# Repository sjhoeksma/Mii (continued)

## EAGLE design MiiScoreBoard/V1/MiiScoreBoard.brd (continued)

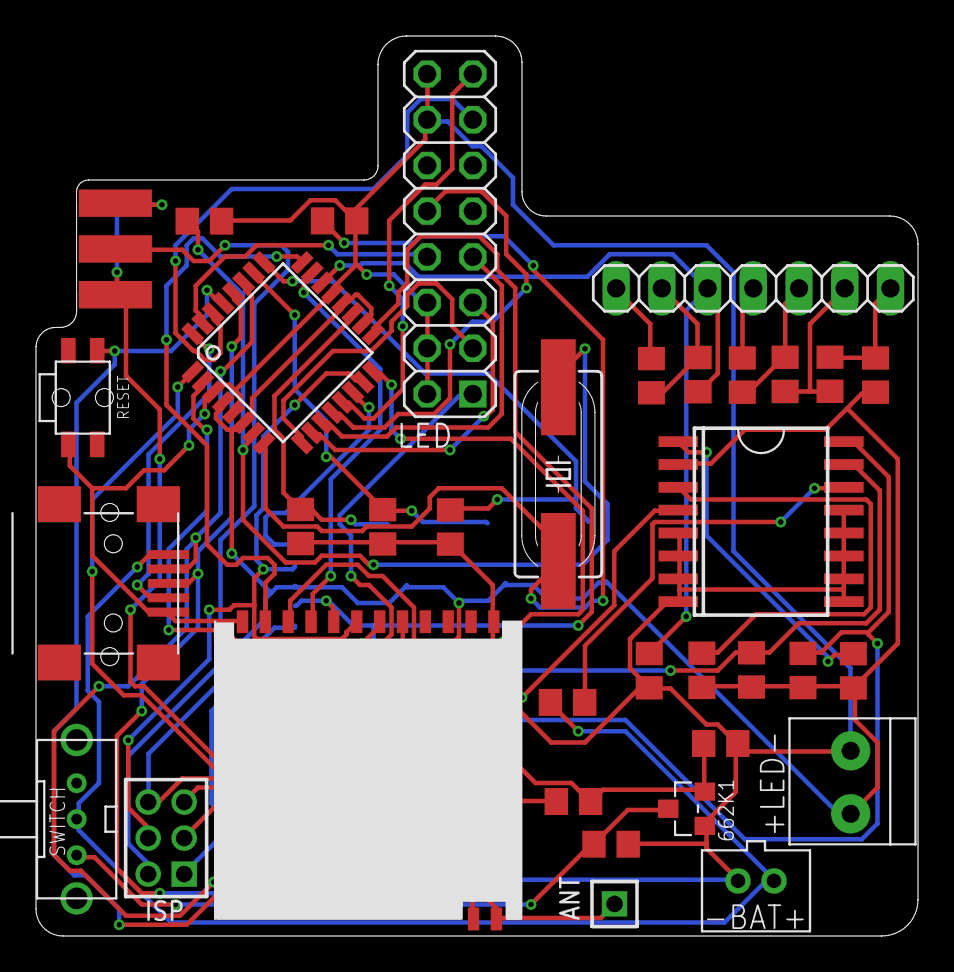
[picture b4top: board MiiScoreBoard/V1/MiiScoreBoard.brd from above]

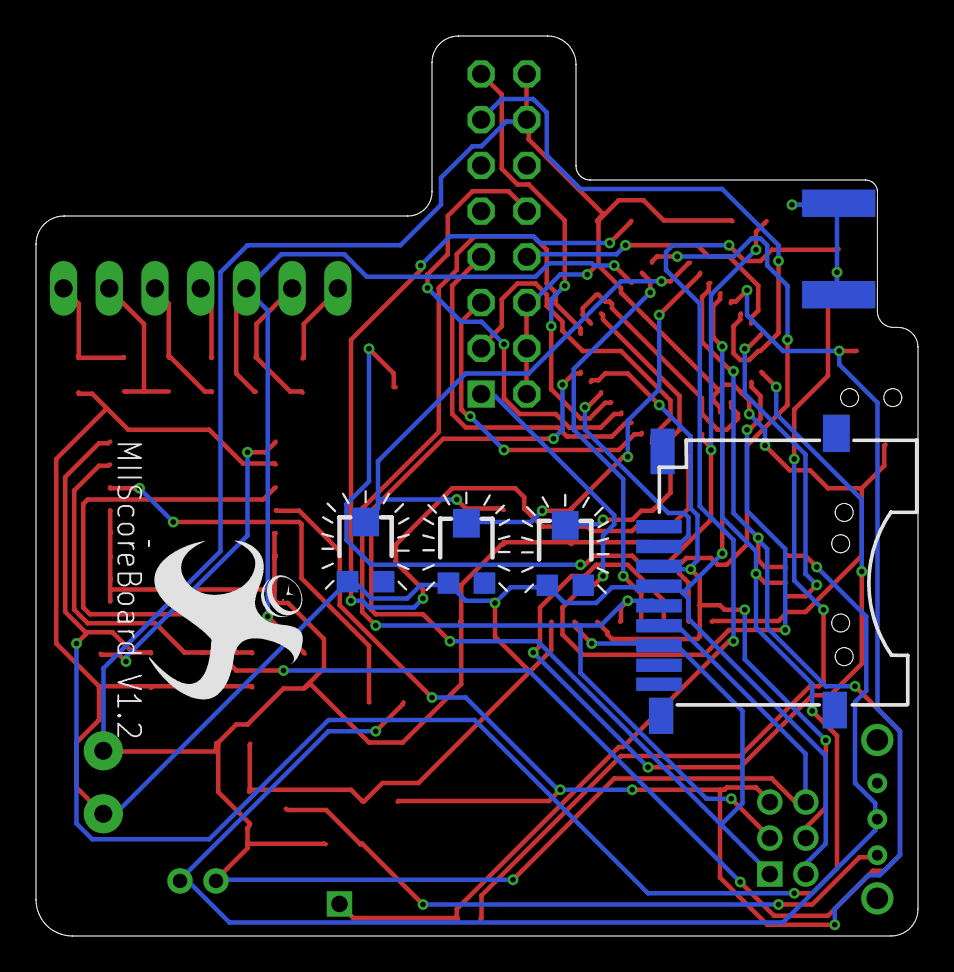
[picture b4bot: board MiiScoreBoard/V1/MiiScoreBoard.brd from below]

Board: 2 copper layers, 49.0 x 50.0 mm, 40 parts (5 on the bottom side), 40 nets.

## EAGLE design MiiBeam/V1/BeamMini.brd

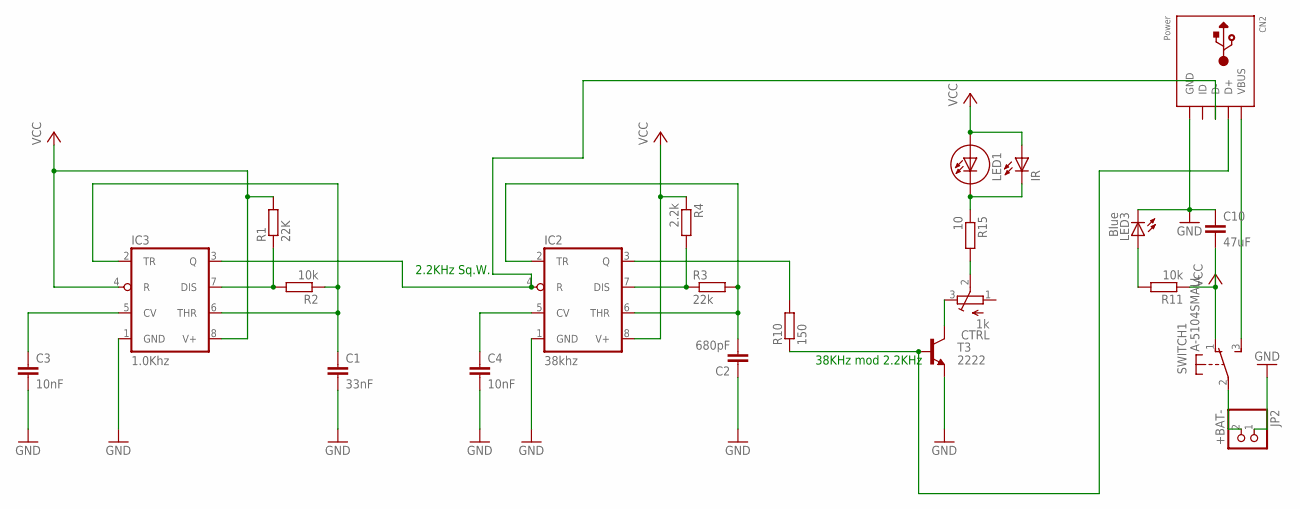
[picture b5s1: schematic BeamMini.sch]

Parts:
C1: 33nF; C0805
C2: 680pF; C0805
C3, C4: 10nF; C0805
C10: 47uF; C0805
CN2: Power; USB-MINIB
CTRL: 1k; TC33X
IC2: 38khz; SO08
IC3: 1.0Khz; SO08
IR: LED5MM
JP2: +BAT-; 1X02M
LED1: LUXEON-2
LED3: Blue; CHIP-LED0805
R1: 22K; M0805
R2, R11: 10k; M0805
R3: 22k; M0805
R4: 2.2k; M0805
R10: 150; M0805
R15: 10; R0805
SWITCH: A-5104SMALL; A-5104-SMALL
T3: 2222; SOT23

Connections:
CTRL: CTRL.2 (S), R15.2
GND: C1.2, C2.1, C3.2, C4.2, C10.1, CN2.GND, IC2.1 (GND), IC3.1 (GND), JP2.1, LED3.C, T3.2 (E)
unnamed: IC3.7 (DIS), R1.1, R2.2
unnamed: C3.1, IC3.5 (CV)
unnamed: C2.2, IC2.2 (TR), IC2.6 (THR), R3.2
unnamed: IC2.7 (DIS), R3.1, R4.2
unnamed: CN2.D-, IC2.4 (R), IC3.3 (Q)
unnamed: C4.1, IC2.5 (CV)
unnamed: IC2.3 (Q), R10.2
unnamed: JP2.2, SWITCH.2
unnamed: C1.1, IC3.2 (TR), IC3.6 (THR), R2.1
unnamed: CN2.D+, R10.1, T3.1 (B)
unnamed: IR.K (C), LED1.C, R15.1
unnamed: CTRL.3 (E), T3.3 (C)
unnamed: LED3.A, R11.2
unnamed: CN2.VBUS, SWITCH.3 (S)
VCC: C10.2, IC2.8 (V+), IC3.4 (R), IC3.8 (V+), IR.A, LED1.A, R1.2, R4.1, R11.1, SWITCH.1 (O)

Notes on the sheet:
2.2KHz Sq.W.
38KHz mod 2.2KHz

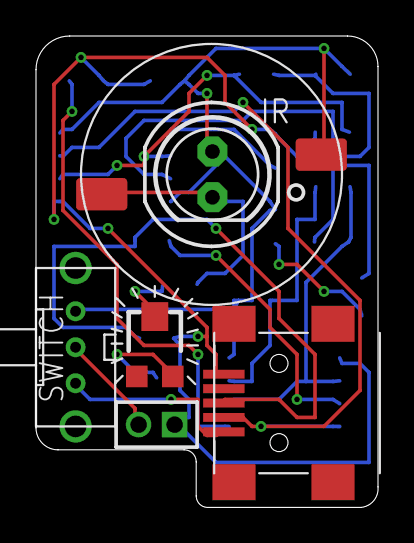
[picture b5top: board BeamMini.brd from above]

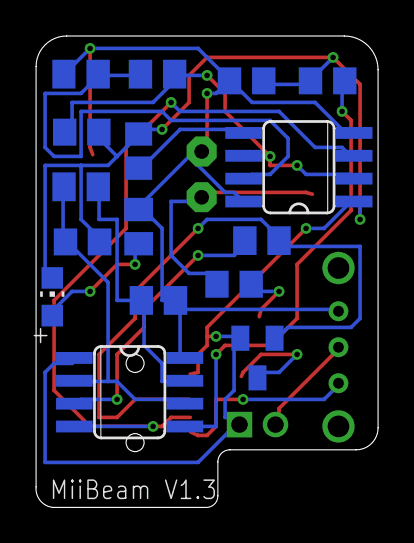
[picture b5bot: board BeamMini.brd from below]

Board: 2 copper layers, 19.0 x 26.2 mm, 22 parts (16 on the bottom side), 17 nets.

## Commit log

2017-02-24 Rebuild of Github repository
